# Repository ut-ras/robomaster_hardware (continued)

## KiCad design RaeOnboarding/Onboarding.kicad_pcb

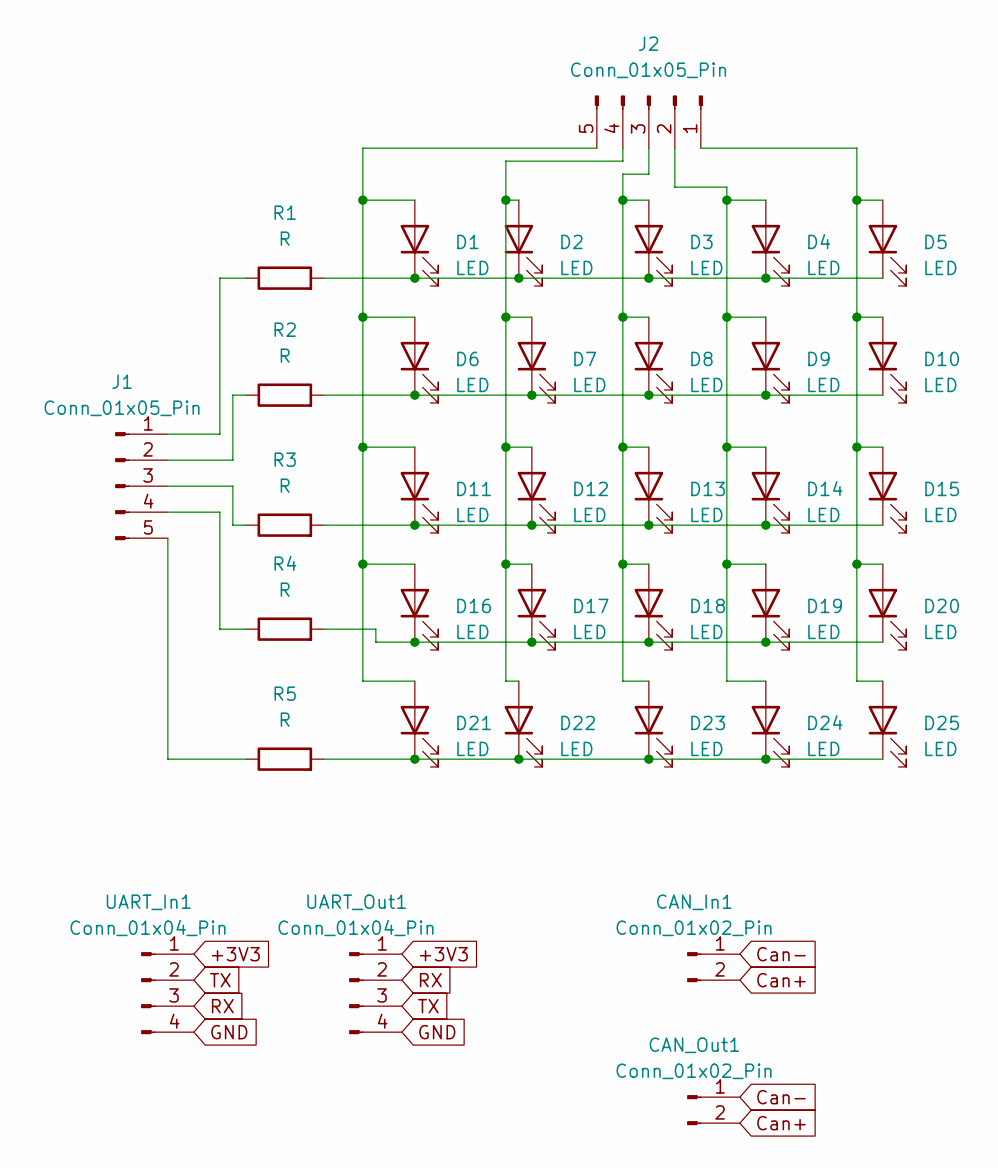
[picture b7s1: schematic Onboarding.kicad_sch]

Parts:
CAN_In1: Conn_01x02_Pin; PinHeader_1x02_P2.54mm_Horizontal
CAN_Out1: Conn_01x02_Pin; PinHeader_1x02_P2.54mm_Horizontal
D1, D2, D3, D4, D5, D6, D7, D8, D9, D10, D11, D12, D13, D14, D15, D16, D17, D18, D19, D20, D21, D22, D23, D24, D25: LED; LED_D3.0mm
J1, J2: Conn_01x05_Pin; Harwin_M20-89005xx_1x05_P2.54mm_Horizontal
R1, R2, R3, R4, R5: R; R_Axial_DIN0207_L6.3mm_D2.5mm_P7.62mm_Horizontal
UART_In1: Conn_01x04_Pin; PinHeader_1x04_P2.54mm_Horizontal
UART_Out1: Conn_01x04_Pin; PinHeader_1x04_P2.54mm_Horizontal

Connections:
+3V3: UART_In1.1, UART_Out1.1
Can+: CAN_In1.2, CAN_Out1.2
Can-: CAN_In1.1, CAN_Out1.1
GND: UART_In1.4, UART_Out1.4
unnamed: D1.2 (A), D6.2 (A), D11.2 (A), D16.2 (A), D21.2 (A), J2.5
unnamed: D1.1 (K), D2.1 (K), D3.1 (K), D4.1 (K), D5.1 (K), R1.2
unnamed: D5.2 (A), D10.2 (A), D15.2 (A), D20.2 (A), D25.2 (A), J2.1
unnamed: D6.1 (K), D7.1 (K), D8.1 (K), D9.1 (K), D10.1 (K), R2.2
unnamed: D11.1 (K), D12.1 (K), D13.1 (K), D14.1 (K), D15.1 (K), R3.2
unnamed: D2.2 (A), D7.2 (A), D12.2 (A), D17.2 (A), D22.2 (A), J2.4
unnamed: D3.2 (A), D8.2 (A), D13.2 (A), D18.2 (A), D23.2 (A), J2.3
unnamed: D4.2 (A), D9.2 (A), D14.2 (A), D19.2 (A), D24.2 (A), J2.2
unnamed: D16.1 (K), D17.1 (K), D18.1 (K), D19.1 (K), D20.1 (K), R4.2
unnamed: D21.1 (K), D22.1 (K), D23.1 (K), D24.1 (K), D25.1 (K), R5.2
unnamed: J1.1, R1.1
unnamed: J1.2, R2.1
unnamed: J1.3, R3.1
unnamed: J1.4, R4.1
unnamed: J1.5, R5.1
RX: UART_In1.3, UART_Out1.2
TX: UART_In1.2, UART_Out1.3

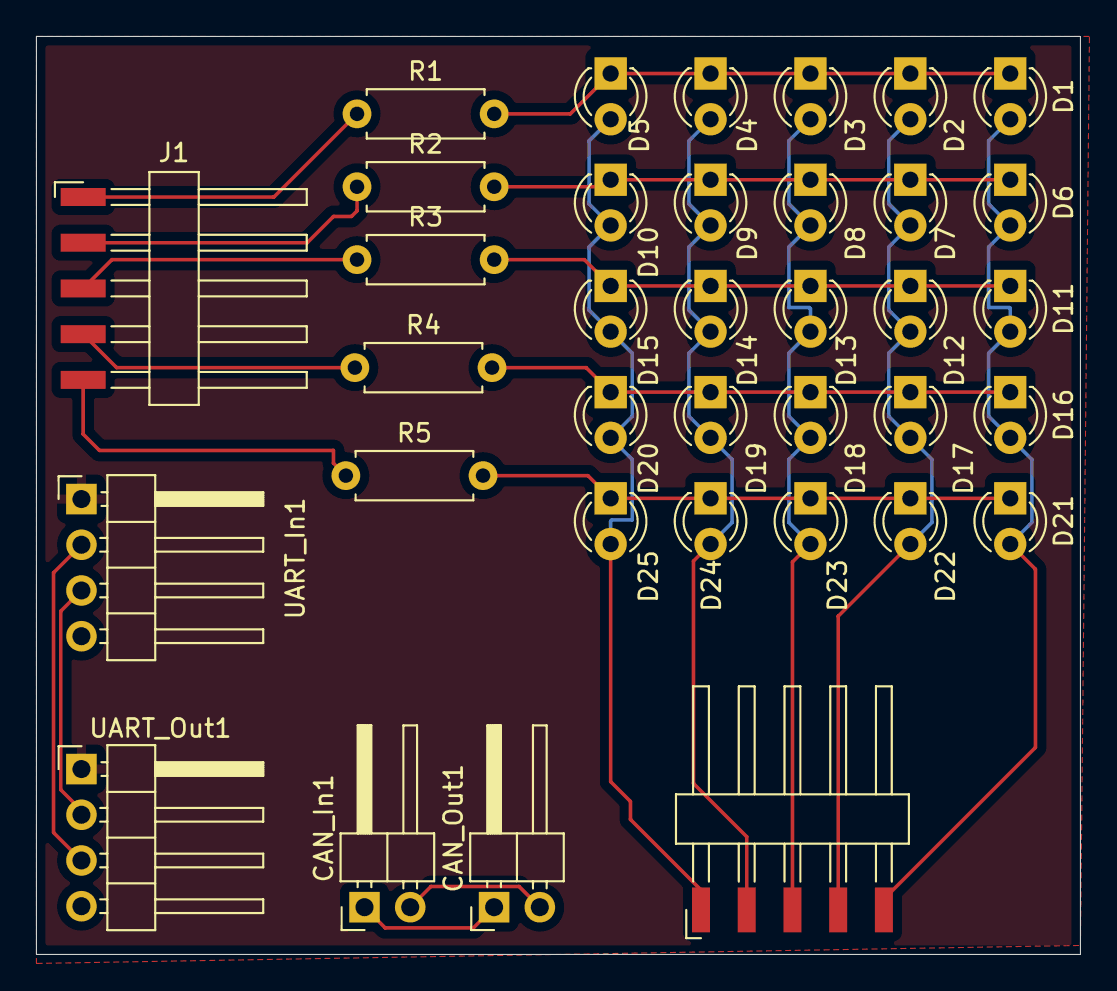
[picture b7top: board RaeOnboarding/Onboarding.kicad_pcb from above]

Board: 2 copper layers, 58.0 x 51.0 mm, 36 parts (0 on the bottom side), 21 nets.
